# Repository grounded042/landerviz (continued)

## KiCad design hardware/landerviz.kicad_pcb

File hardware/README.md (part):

# LanderViz revision-A hardware

**2026-11-07:** the reviewed [PGA2350 carrier](carrier/README.md) Rev A
bare boards are ordered from OSH Park. The 90 × 75 mm two-layer design is
frozen; see [order status](carrier/ORDER_STATUS.md),
[manufacturing release](carrier/releases/rev-a/README.md) and
[parts sourcing](carrier/SHOPPING.md). The processor purchase assumes A4
silicon; user assembly and the PGA2350 firmware port remain ahead.
Open [the carrier project](carrier/landerviz-carrier.kicad_pro) in KiCad.
The existing `landerviz.kicad_*` files and historical sections below remain
the preserved bare-RP2354A candidate, which was not ordered.

This directory contains the KiCad 10 schematic and, after schematic approval,
the printed-circuit-board layout for LanderViz revision A.

The source of truth for requirements and open decisions is
[`../PCB.md`](../PCB.md). Do not infer electrical decisions from a footprint or
unfinished sheet when `PCB.md` still marks the item open.

## Tooling

The project currently targets KiCad 10.0.6, the version installed on the
design Mac. Firmware and software continue to use the repository's Nix flake.
The pinned Nix package set marks KiCad broken on Apple Silicon, so KiCad is not
added to the development shell until that package is usable. Open
`landerviz.kicad_pro` with the installed KiCad application.

Generated backups, lock files, and working manufacturing outputs are ignored.
The exact ordered carrier Gerber ZIP and its manifest are preserved under
`carrier/releases/rev-a/`. Source
schematics, board files, symbol/footprint libraries, design rules, and reviewed
fabrication settings belong in version control.

The project-local `sym-lib-table` and `fp-lib-table` deliberately name only the
KiCad libraries used by the capture. They also make command-line checks and a
fresh checkout independent of this Mac's global KiCad-library preferences.
`landerviz.kicad_sym` contains the reviewed TPS25821 and TLV75533PDBV pin
definitions, RP2354A, and the approved TPS22953DQC input-switch definition.
The schematic is ordinary KiCad source; opening or editing it
does not run Python or install a Python package.

## Upstream electrical reference

Raspberry Pi's `RP2350A Minimal` KiCad design R4-S1 (July 2026) is a read-only
reference for circuitry shared with RP2354A:

- <https://pip.raspberrypi.com/documents/RP-010328-CA-RP2350A%20Minimal%20KiCAD.zip>
- SHA-256:
  `c0b858d78f56fa271a827064198e8ee81e4ec246234ce6659be8a1fcd877d06b`
- License: MIT, Copyright Raspberry Pi Ltd 2026

The archive is not vendored. Its local processor regulator placement is used
as a reference-derived layout input, with attribution in `REFERENCE_LICENSE.txt`.
The complete reference board is not copied. In particular, do not copy its external QSPI flash,
Micro-USB connector, board outline, or routing. LanderViz uses RP2354A with 2
MB of in-package flash. See `PCB.md` for the exact reuse boundary.

## Capture plan

The initial hierarchy deliberately separates review domains:

| Sheet | Responsibility |
|---|---|
| `mcu.kicad_sch` | RP2354A, 12 MHz clock, core supply, decoupling, RUN, BOOTSEL, and SWD |
| `usb_power.kicad_sch` | both USB-C ports, native and PIO USB data paths, 5 V protection/switching, 3.3 V regulation, and bulk capacitance |
| `audio.kicad_sch` | stereo TRS input, per-channel bias, protection, anti-alias filters, ADC inputs, and test points |
| `controls_display.kicad_sch` | EC11 encoder, push switch, I2C level translation, and LCD connector |

Capture proceeds in reviewable slices. Component values that remain open in
`PCB.md` must be selected from calculations and manufacturer documentation,
not copied from an unrelated example.

## Current capture status — 2026-11-02

### Physical layout draft — 2026-11-04

Open `landerviz.kicad_pcb` in KiCad's PCB Editor. All 79 schematic footprints
now have working positions inside the 48 by 42 mm outline and retain their
original schematic paths, component fields, and pad connections. Three
board-only M2 mounting holes are provisional. All purchased components are
on top; the twelve bare test pads are on the underside, without adding an
assembly operation. The user approved larger and rectangular outline studies.
The regulator, crystal, processor supplies, USB, stereo audio, display,
encoder, and service connections are routed on the approved four-layer board.

Upstream USB-C and the audio jack face left. Moonlander USB-C faces right,
opposite the inputs. The display connector's opening faces outward at the top
edge, and the encoder is at the lower right. The audio jack
requires an edge notch, which is included in the draft outline. The layout
now uses four copper layers. Physical packing fits; electrical placement and routing are
still under review. The power blocks are now local, and the analog and display
groups are closer to their target positions than in the 40 mm study. Processor
bypass capacitors have priority around their respective
supply pins. Component reference text is on the fabrication layers (the assembly
drawing), keeping the tiny top side free of unreadable overlapping references.

KiCad's initial placement check reports zero schematic-parity findings (the
board components and connections match the schematic). The outline closes,
and the current placement has no courtyard overlaps, shorts, or copper-edge
clearance findings. A courtyard is the reserved assembly space around a part.
The board has zero unconnected findings. The USB locating-hole clearances
and library mismatches are resolved; see `LIBRARY_CHANGES.md` for the exact
local variants. The processor's farthest core-supply bypass, C10, is now
4.7 microfarads, as required by the datasheet, and closer to pin 23.
Ground copper fills all four layers and is joined by
stitching vias; there are no disconnected ground findings. A stitching via
is a plated hole that joins ground copper on the two sides.
There are no shorts, trace-clearance failures, courtyard overlaps, or
schematic-parity findings. No findings were waived. USB geometry/impedance, power, analog, and
assembly reviews also remain necessary.
This draft is not manufacturing-ready.

### Four-layer stack and checks — 2026-11-04

The selected working stack is JLCPCB's nominal 1.6 mm `JLC04161H-3313`, using
the manufacturer's [published copper and insulation dimensions](https://jlcpcb.com/impedance):

| Position | KiCad layer | Role |
|---|---|---|
| Top | `F.Cu` | components, local power/analog connections, USB escapes, ground fill |
| Inner 1 | `In1.Cu` | dedicated ground; no routed tracks |
| Inner 2 | `In2.Cu` | additional signal routing and ground fill |
| Bottom | `B.Cu` | existing USB/power/signal routes, bare probes, ground fill |

Outer copper is 0.035 mm; inner copper is 0.0152 mm. The insulating spacings
are 0.0994 / 1.265 / 0.0994 mm. The insulating material is FR-4, a glass/epoxy
laminate. KiCad retains nominal 1.6 mm board thickness and blue/white finish;
the 0.01 mm mask values remain rendering approximations. The selected stack
must be specified in the fabrication order, not left to an arbitrary stack.

`In1.Cu` fills as one connected ground region. The regulator has named
inner-layer keepouts beneath the inductor and switching node, following
RP2350 datasheet section 6.3.8.1 / Figure 27. The top-side fill keepout follows
the existing switching polygon's edge so that the required LX connection
remains intact. The reference regulator's component placement is retained.
C10 is corrected to the datasheet's 4.7 microfarad bypass for DVDD pin 23.

New escapes use ordinary 0.4 mm diameter / 0.2 mm drilled through vias;
these span all four layers. The project's minimum drill and via diameters now
match those values, within JLCPCB's [published capabilities](https://jlcpcb.com/capabilities/pcb-capabilities/).
The minimum annular ring remains 0.1 mm and general copper clearance 0.2 mm.
There are no blind/buried vias or newly assumed filling/capping processes.
This also resolves the previous three 0.2 mm controller-hole drill findings.

C12 moved 0.1 mm upward, with its ground via also moved upward. The right ADC
probe now connects through a small via inside the bare bottom test pad, with
shorter inner-layer branches to the series resistor and clamp. The probe has
no solder-paste aperture. Obsolete display-data detours and trial stubs were
removed. The LCD SDA via at (27.8, 8.8) mm moved to (27.8, 8.9) mm to improve
the ground reference beneath the downstream USB data pair.

Validation with KiCad 10.0.6: zero unconnected items, shorts, trace-clearance
errors, courtyard overlaps, dangling tracks/vias, or schematic-parity findings.
A separate geometric check sampled USB track centers and edges every 0.1 mm,
excluding 0.8 mm around USB via launches: all 3,798 samples have ground on
the adjacent inner layer. This verifies sampled reference coverage; it does
not establish 90-ohm differential impedance or USB electrical compliance.

### Board artwork

The working finish is blue solder mask with white silkscreen. Solder mask is
the protective coating over the copper; silkscreen is the printed lettering.
Both sides use those colors in the KiCad stackup. Enable "Use board stackup
colors" in the 3D Viewer if local appearance settings override them. The
fabrication order must separately select the desired color; the preview does
not place or configure an order. Black remains an acceptable alternative, but
mask clearances must be reviewed for that manufacturing option before release.
The stackup retains nominal 1.6 mm thickness with 35 micrometer outer and
15.2 micrometer inner copper; fabrication settings remain unreleased.

The underside has a bold `LANDERVIZ` wordmark centered at (27, 21) mm from
the upper-left board corner, with `REV A / AUDIO IN. LIGHT OUT.` at (27, 23.5)
mm. The ink clears the probe labels and through-hole hardware. The lander and flowing-ribbon
drawings were removed at the user's request. Decorative drawings are deferred
while the electrical layout is developed. Final routing and test access take
priority over ink. Press Alt+3 in the PCB Editor for KiCad's 3D Viewer and turn
the board over to inspect it; top-side service labels will be finalized after
placement stabilizes.

### Electrical placement review — continuation

The initial 40 mm physical packing was rejected because it did not adequately
preserve local power and analog circuits. See `PLACEMENT_REVIEW.md` for that
history, the subsequent outline comparison, and current routing status. A clean
overlap check must not be presented as complete electrical placement approval.
The current 48 by 42 mm draft follows the user's permission to explore larger
and rectangular outlines.

The processor regulator group now follows the local geometry of the pinned
Raspberry Pi R4-S1 reference, adjusted for this project's pad/courtyard sizes.
Its marked inductor terminal remains connected to the switch node. The crystal
signal paths are routed on top without signal vias. The local regulator
input/feedback/output, switching-node copper, filtered supply, and capacitor
ground returns are now connected. Most processor supply pins now have short
branches to their bypass capacitors, whose ground ends join the back plane.
The U1 pin 20 / C14 supply escape is now connected by a back-side branch;
the clock remains on top and the ground plane stays connected. The wider
3.3 V and 1.1 V distribution is connected. The main input fuse, protected 5 V
trunk, keyboard power switch and bulk reservoir, switched keyboard output,
and fused display feed are now connected. Short 0.25–0.4 mm pad escapes join
0.8–1.0 mm trunks; paired 0.8/0.4 mm vias carry the keyboard output between
layers. These widths need final current/temperature review before release.
The project's minimum trace width is now 0.15 mm for fine-pitch escapes; default
net-class routing width stays at 0.2 mm and local regulator power traces at
0.4 mm. Fabrication-rule signoff remains pending.

`landerviz.kicad_dru` permits 0.10 mm clearance only between the switching
node and C6/C7 pads, allowing the reference-style escape through their pad
gap. Other clearance rules remain unchanged. The local rule is based on
[JLCPCB's 1 oz pad-to-track capability](https://jlcpcb.com/capabilities/pcb-);
changing copper weight requires rechecking it. No findings are suppressed.

Four 0.3 mm drill ground vias join the processor's exposed pad (the large
ground contact underneath the chip) to the back plane. Their interaction with
solder paste and possible solder wicking through the holes must be checked
in assembly review; no premium filled/capped-via process has been selected.

The upstream USB-C A6/B6 and A7/B7 contacts are connected to their respective
data nets and to U3's electrostatic-discharge protection pads. The alternating
contacts join on opposite sides of the connector tail row, avoiding crossed
data nets. U3 has a local ground via. Both upstream and downstream data paths
now continue through their series resistors to the processor. Each signal uses
two layer transitions in the upstream link and four in the downstream link.
The processor-end vias sit outside the exposed pad, under the package body,
with tented mask rather than premium filled/capped vias. Main connector power
is routed. Configuration-channel (CC) wiring is connected on both ports.
The power controller's reference
resistor is connected. Whole-link geometry and impedance review are pending.
This is connectivity/clearance progress, not functional USB or signal-integrity
signoff; the board is not ready to power or order.

Both audio coupling capacitors now face their negative input terminals toward
the jack. C29 moved beside the right analog-to-digital converter (ADC) input.
Both filter-capacitor-to-processor paths stay on the front; the right-channel
resistor/clamp branches use the back as well. Bias, protection, filter ground
returns, and all four audio test pads are connected. Longer analog branches,
probe stubs, and their return paths remain electrical-review items.

The display clock, encoder A, debug clock/data, and reset escapes are now
connected. Display pull-up links, display data, encoder B/press, spare GPIO
probes, and boot-select are connected. R22 is now
at (38.5, 1.8) mm. Ground stitching resolved pockets created by back-side control traces;
the ground fills discard isolated copper. USB shield lugs, the display ground
pin, and U2's three thermal holes use selected solid ground connections, with
solderability still to review. No design-rule findings were waived.

Clipped package-outline ink was removed from the board; the assembly drawings
are retained, and a smaller processor pin-one dot replaces the clipped marker.
The project-owned encoder and inductor footprints retain these changes in
their source files. The edited upstream-library footprints now have matching
project-local variants. A spare-GPIO trace was rerouted around
the audio jack's non-plated mounting hole.

The user approved and the board now implements four copper layers with the
same outline and components. Earlier two-layer experiments that introduced
excessive analog detours or ground fragmentation were discarded. Those
experiments do not prove that a two-layer design is impossible.

The original same-edge USB arrangement and inward-facing LCD opening were
corrected after visual review. The local regulator block and its first traces
were moved to accommodate the left-edge USB input, USB protection was placed
behind that connector, and the probe pads were rechecked against the relocated
through-hole hardware. Pin assignments and the schematic are unchanged.

Underside probe labels: `CLK`/`DIO` are Serial Wire Debug clock/data;
`BL`/`BR` are left/right bias; `AL`/`AR` are left/right analog-to-digital
converter inputs; `GP6`/`GP7` are spare GPIO6/GPIO7 pads. The schematic test-point
references remain visible on the bottom fabrication layer.

The enclosure will be designed after the PCB is ordered, using the user's
library makerspace or a friend's 3D printer. No enclosure supplier is selected.

### MCU core

The MCU-core sheet is populated and the project-level MCU sheet symbol exposes
the frozen USB, audio, encoder, and display signals. The capture
includes the RP2354A, its 1.1 V switching-regulator network, supply bypassing,
12 MHz crystal, BOOTSEL and reset buttons, Serial Wire Debug (SWD) pads, native
USB and PIO-USB series resistors, and explicit no-connect flags on unused pins.

The exact L1 inductor, Y1 crystal, reset/BOOTSEL switches, RP2354A, and ordinary
passives now have manufacturer, JLCPCB/LCSC catalog, and footprint assignments.
L1 uses a project-local footprint copied from Abracon's land pattern; its marked
terminal is **pad 1, the +1V1 output side**, matching Raspberry Pi's R4-S1
reference. The fabrication dot was corrected after independent review; the
assembler must verify the physical dot orientation, not just the placement
rotation number. C6/C7/C9/C10 now specify the reference-design Murata
`GRM155R60J475ME47D` (JLCPCB `C82453`) instead of the unqualified CCTC
substitute. C9 has an independent ground via; the switching return uses two
adjacent vias. See [`REVIEW_RESOLUTION.md`](REVIEW_RESOLUTION.md).
The Serial Wire Debug (SWD)
and rail test points are 2 mm exposed surface pads and require no purchased
component.

### USB and power

The USB/power sheet is electrically captured and connected to the MCU sheet:

- J1 is the upstream USB-C sink/device port. Each configuration-channel (CC)
  pin has its own 5.1 kilohm pull-down; the two orientation copies of each USB
  data signal join before the MCU's 27 ohm series resistor.
- J2 is the downstream USB-C source/host port. A TPS25821 monitors both CC
  pins, advertises 1.5 A, and switches the keyboard's 5 V VBUS rail only after
  attachment. Both connector orientations join before the MCU's 22 ohm series
  resistors.
- Each USB data pair has a TPD2EUSB30DRTR two-channel electrostatic-discharge
  (ESD) protector. ESD means a short high-voltage event such as a static shock.
- A stocked 2 A-hold LUTE `1206L200/16NR` resettable polymer fuse protects the
  input. Its hold current falls to 1.42 A at 60°C, so it does not establish
  a 1.5 A continuous port rating across temperature. Supported ambient/current
  limits still require a release decision.
- The proven 470 microfarad reservoir is on the protected input side
  of the TPS25821, after the approved TPS22953 controlled-charging input
  switch. Its keyboard-port output has 4.7 microfarads, below the
  controller's 10 microfarad limit.
  C25 now sits beside J2 at (37.1,14.2) mm. U6 ramps the reservoir and every
  existing powered branch; only 1 µF bypass and the enable circuit precede it.
  Its estimated startup behavior still requires assembled-board validation.
  See [`INPUT_POWER_PROPOSAL.md`](INPUT_POWER_PROPOSAL.md) for the approved
  five-part circuit, enable threshold, ramp calculation and reverse-blocking limits.
- A TLV75533PDBVR fixed-output, 500 mA low-dropout regulator creates the 3.3 V
  logic rail. The display receives a separately protected 5 V branch.
- Labeled 5 V, 3.3 V, and ground test points are included.

The USB/power page has no electrical-rules-check findings. The exported netlist
was also checked to confirm that connector-facing data nets stop at the correct
side of each series resistor; the corresponding chip-facing nets reach only
the intended native-USB or PIO-USB pin.

Both USB-C ports use the GCT `USB4105-GF-A-060`. The TPS25821 uses a
project-local footprint built from TI's `DSS0012B` recommended WSON land pattern;
**WSON** means a very small leadless package with an exposed thermal pad. The
470 microfarad reservoir, display-branch fuse, reset/BOOTSEL switches, crystal,
inductor, and test-pad style are also assigned. Placement, cable clearance, and
assembly-orientation review remain fabrication gates, but no schematic part is
waiting for a footprint.

### Stereo audio frontend

The audio sheet is populated, electrically connected to GPIO26/ADC0 and
GPIO27/ADC1, and clean under the project-level electrical rules check. Tip is
left, ring is right, and sleeve is ground on J3. Each channel is independent:

- A 10 microfarad coupling capacitor blocks direct current from the mixer. If
  the selected part is polarized, its positive terminal faces the bias node.
- Two 22 kilohm, 1% resistors bias that node near half of 3.3 V. They present
  an approximately 11 kilohm load; with 10 microfarads, the nominal high-pass
  corner is about 1.45 Hz.
- A 10 kilohm, 1% series resistor and 2.2 nanofarad C0G, 5% capacitor form a
  first-order low-pass at about 7.2 kHz. This is intentional modest
  anti-aliasing for the firmware's 15.625 kHz-per-channel sampling, whose
  Nyquist frequency is about 7.8 kHz.
- A BAT54S-7-F dual Schottky diode in SOT-23 clamps the ADC node toward ground
  and 3.3 V. The series resistor limits fault and unpowered-input current. The
  package and ordering code match the
  [Diodes Incorporated datasheet](https://www.diodes.com/datasheet/download/BAT54S.pdf);
  leakage and assembly stock remain bill-of-materials release checks.
- TP7/TP9 expose the left/right bias nodes; TP8/TP10 expose the left/right ADC
  nodes.

J3 is frozen as the CUI `SJ1-3523N` right-angle through-hole jack using KiCad's
matching `Jack_3.5mm_CUI_SJ1-3523N_Horizontal` footprint. JLCPCB/LCSC catalog
identifier `C20182914` records the sourcing target; assembly inventory must be
rechecked when the order is released. C26/C27 are polarized 10 microfarad,
16 V surface-mount electrolytics, with the positive terminal toward the biased
ADC node. Audio test points use the same 2 mm exposed pads as the power and SWD
points. Assembled-board bring-up must confirm bias voltage, silence/noise,
bass response, high-frequency texture, and clipping before firmware gain or
calibration constants are retuned.

### Encoder and external display

The controls/display sheet now captures the proven encoder circuit and
revision-A serial-display interface:

- SW3 is frozen as the top-facing Bourns `PEC12R-4120F-S0012`, JLCPCB/LCSC
  `C143801`: 12 detents, 12 pulses, a push switch, and a 20 mm shaft. It
  connects encoder A, encoder B, and the push switch to GPIO4, GPIO5, and
  GPIO8. Its encoder common and other switch terminal return to digital ground.
  Firmware supplies all three pull-ups and debounce/decoding; the PCB adds no
  filtering that could change the validated behavior. This no-bushing variant
  requires PCB/enclosure support close to the control so that repeated pushes
  do not flex the board.
- Q1 and Q2 are BSS138 N-channel MOSFETs
  (metal-oxide-semiconductor field-effect transistors) in SOT-23
  (small-outline transistor) packages. Their sources face the 3.3 V MCU bus,
  drains face the 5 V display bus, and gates connect to 3.3 V. This is the same
  bidirectional open-drain I2C (Inter-Integrated Circuit) level-shifter
  topology demonstrated by the breadboard breakout. The schematic pin order
  matches the
  [onsemi BSS138 datasheet](https://www.onsemi.com/download/data-sheet/pdf/bss138-d.pdf).
- R20/R21 are populated 4.7 kilohm, 1% pull-ups on the 3.3 V side. R22/R23 are
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
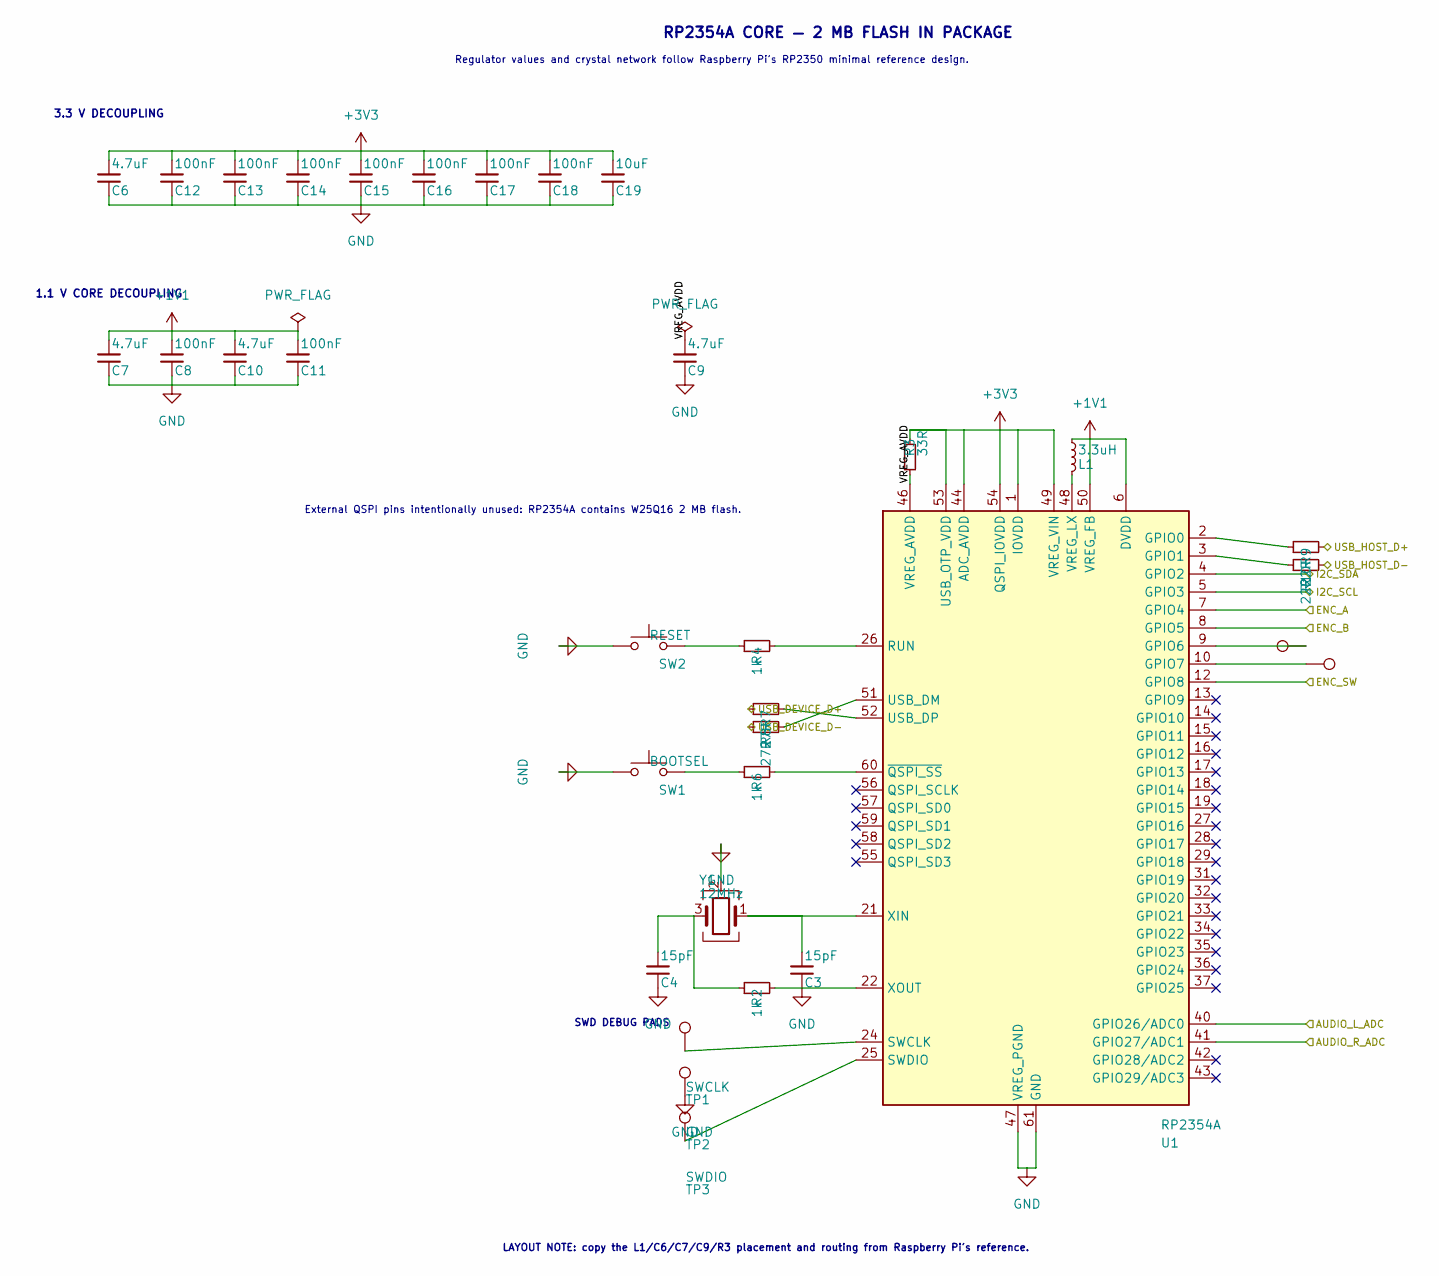
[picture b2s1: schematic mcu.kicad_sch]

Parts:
C3, C4: 15pF; C_0402_1005Metric; MPN 0402CG150J500NT; LCSC C1548
C6, C7, C9, C10: 4.7uF; C_0402_1005Metric; MPN GRM155R60J475ME47D; LCSC C82453
C8, C11, C12, C13, C14, C15, C16, C17, C18: 100nF; C_0402_1005Metric; MPN CL05B104KO5NNNC; LCSC C1525
C19: 10uF; C_0402_1005Metric; MPN TCC0402X5R106M6R3ATR; LCSC C48543727
L1: 3.3uH; L_Abracon_AOTA-B201610S3R3-101-T; MPN AOTA-B201610S3R3-101-T; LCSC C42411119
R2, R4, R6: 1k; R_0402_1005Metric; MPN 0402WGF1001TCE; LCSC C11702
R3: 33R; R_0402_1005Metric; MPN 0402WGF330JTCE; LCSC C25105
R7, R8: 27R; R_0402_1005Metric; MPN 0402WGF270JTCE; LCSC C25100
R9, R10: 22R; R_0402_1005Metric; MPN 0402WGF220JTCE; LCSC C25092
SW1: BOOTSEL; SW_Push_1P1T_XKB_TS-1187A; MPN TS-1187A-B-A-B; LCSC C318884
SW2: RESET; SW_Push_1P1T_XKB_TS-1187A; MPN TS-1187A-B-A-B; LCSC C318884
TP1: SWCLK; TestPoint_Pad_D2.0mm
TP2: GND; TestPoint_Pad_D2.0mm
TP3: SWDIO; TestPoint_Pad_D2.0mm
TP11: GPIO6; TestPoint_Pad_D2.0mm
TP12: GPIO7; TestPoint_Pad_D2.0mm
U1: RP2354A; QFN-60-1EP_7x7mm_P0.4mm_EP3.4x3.4mm_LanderViz; MPN RP2354A; LCSC C41378174
Y1: 12MHz; Crystal_SMD_3225-4Pin_3.2x2.5mm; MPN ABM8-272-T3; LCSC C20625731

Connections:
+1V1: C7.1, C8.1, C10.1, C11.1, L1.1, U1.6 (DVDD), U1.23 (DVDD), U1.39 (DVDD), U1.50 (VREG_FB)
+3V3: C6.1, C12.1, C13.1, C14.1, C15.1, C16.1, C17.1, C18.1, C19.1, R3.1, U1.1 (IOVDD), U1.11 (IOVDD), U1.20 (IOVDD), U1.30 (IOVDD), U1.38 (IOVDD), U1.44 (ADC_AVDD), U1.45 (IOVDD), U1.49 (VREG_VIN), U1.53 (USB_OTP_VDD), U1.54 (QSPI_IOVDD); also elsewhere on the board
/Audio frontend/AUDIO_L_ADC: U1.40 (GPIO26/ADC0); also elsewhere on the board
/Audio frontend/AUDIO_R_ADC: U1.41 (GPIO27/ADC1); also elsewhere on the board
/ENC_A: U1.7 (GPIO4); also elsewhere on the board
/ENC_B: U1.8 (GPIO5); also elsewhere on the board
/ENC_SW: U1.12 (GPIO8); also elsewhere on the board
/I2C_SCL: U1.5 (GPIO3); also elsewhere on the board
/I2C_SDA: U1.4 (GPIO2); also elsewhere on the board
/MCU core/VREG_AVDD: C9.1, R3.2, U1.46 (VREG_AVDD)
/USB and power/USB_DEVICE_D+: R7.1; also elsewhere on the board
/USB and power/USB_DEVICE_D-: R8.1; also elsewhere on the board
/USB and power/USB_HOST_D+: R9.2; also elsewhere on the board
/USB and power/USB_HOST_D-: R10.2; also elsewhere on the board
unnamed: C4.1, R2.1, Y1.3
unnamed: R4.1, SW2.2
unnamed: R6.1, SW1.2
unnamed: R9.1, U1.2 (GPIO0)
unnamed: R10.1, U1.3 (GPIO1)
unnamed: TP11.1, U1.9 (GPIO6)
unnamed: TP12.1, U1.10 (GPIO7)
unnamed: R4.2, U1.26 (RUN)
unnamed: TP1.1, U1.24 (SWCLK)
unnamed: TP3.1, U1.25 (SWDIO)
unnamed: R8.2, U1.51 (USB_DM)
unnamed: R7.2, U1.52 (USB_DP)
unnamed: L1.2, U1.48 (VREG_LX)
unnamed: C3.1, U1.21 (XIN), Y1.1
unnamed: R6.2, U1.60 (~QSPI_SS)

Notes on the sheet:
RP2354A CORE — 2 MB FLASH IN PACKAGE
Regulator values and crystal network follow Raspberry Pi's RP2350 minimal reference design.
3.3 V DECOUPLING
1.1 V CORE DECOUPLING
SWD DEBUG PADS
External QSPI pins intentionally unused: RP2354A contains W25Q16 2 MB flash.
LAYOUT NOTE: copy the L1/C6/C7/C9/R3 placement and routing from Raspberry Pi's reference.

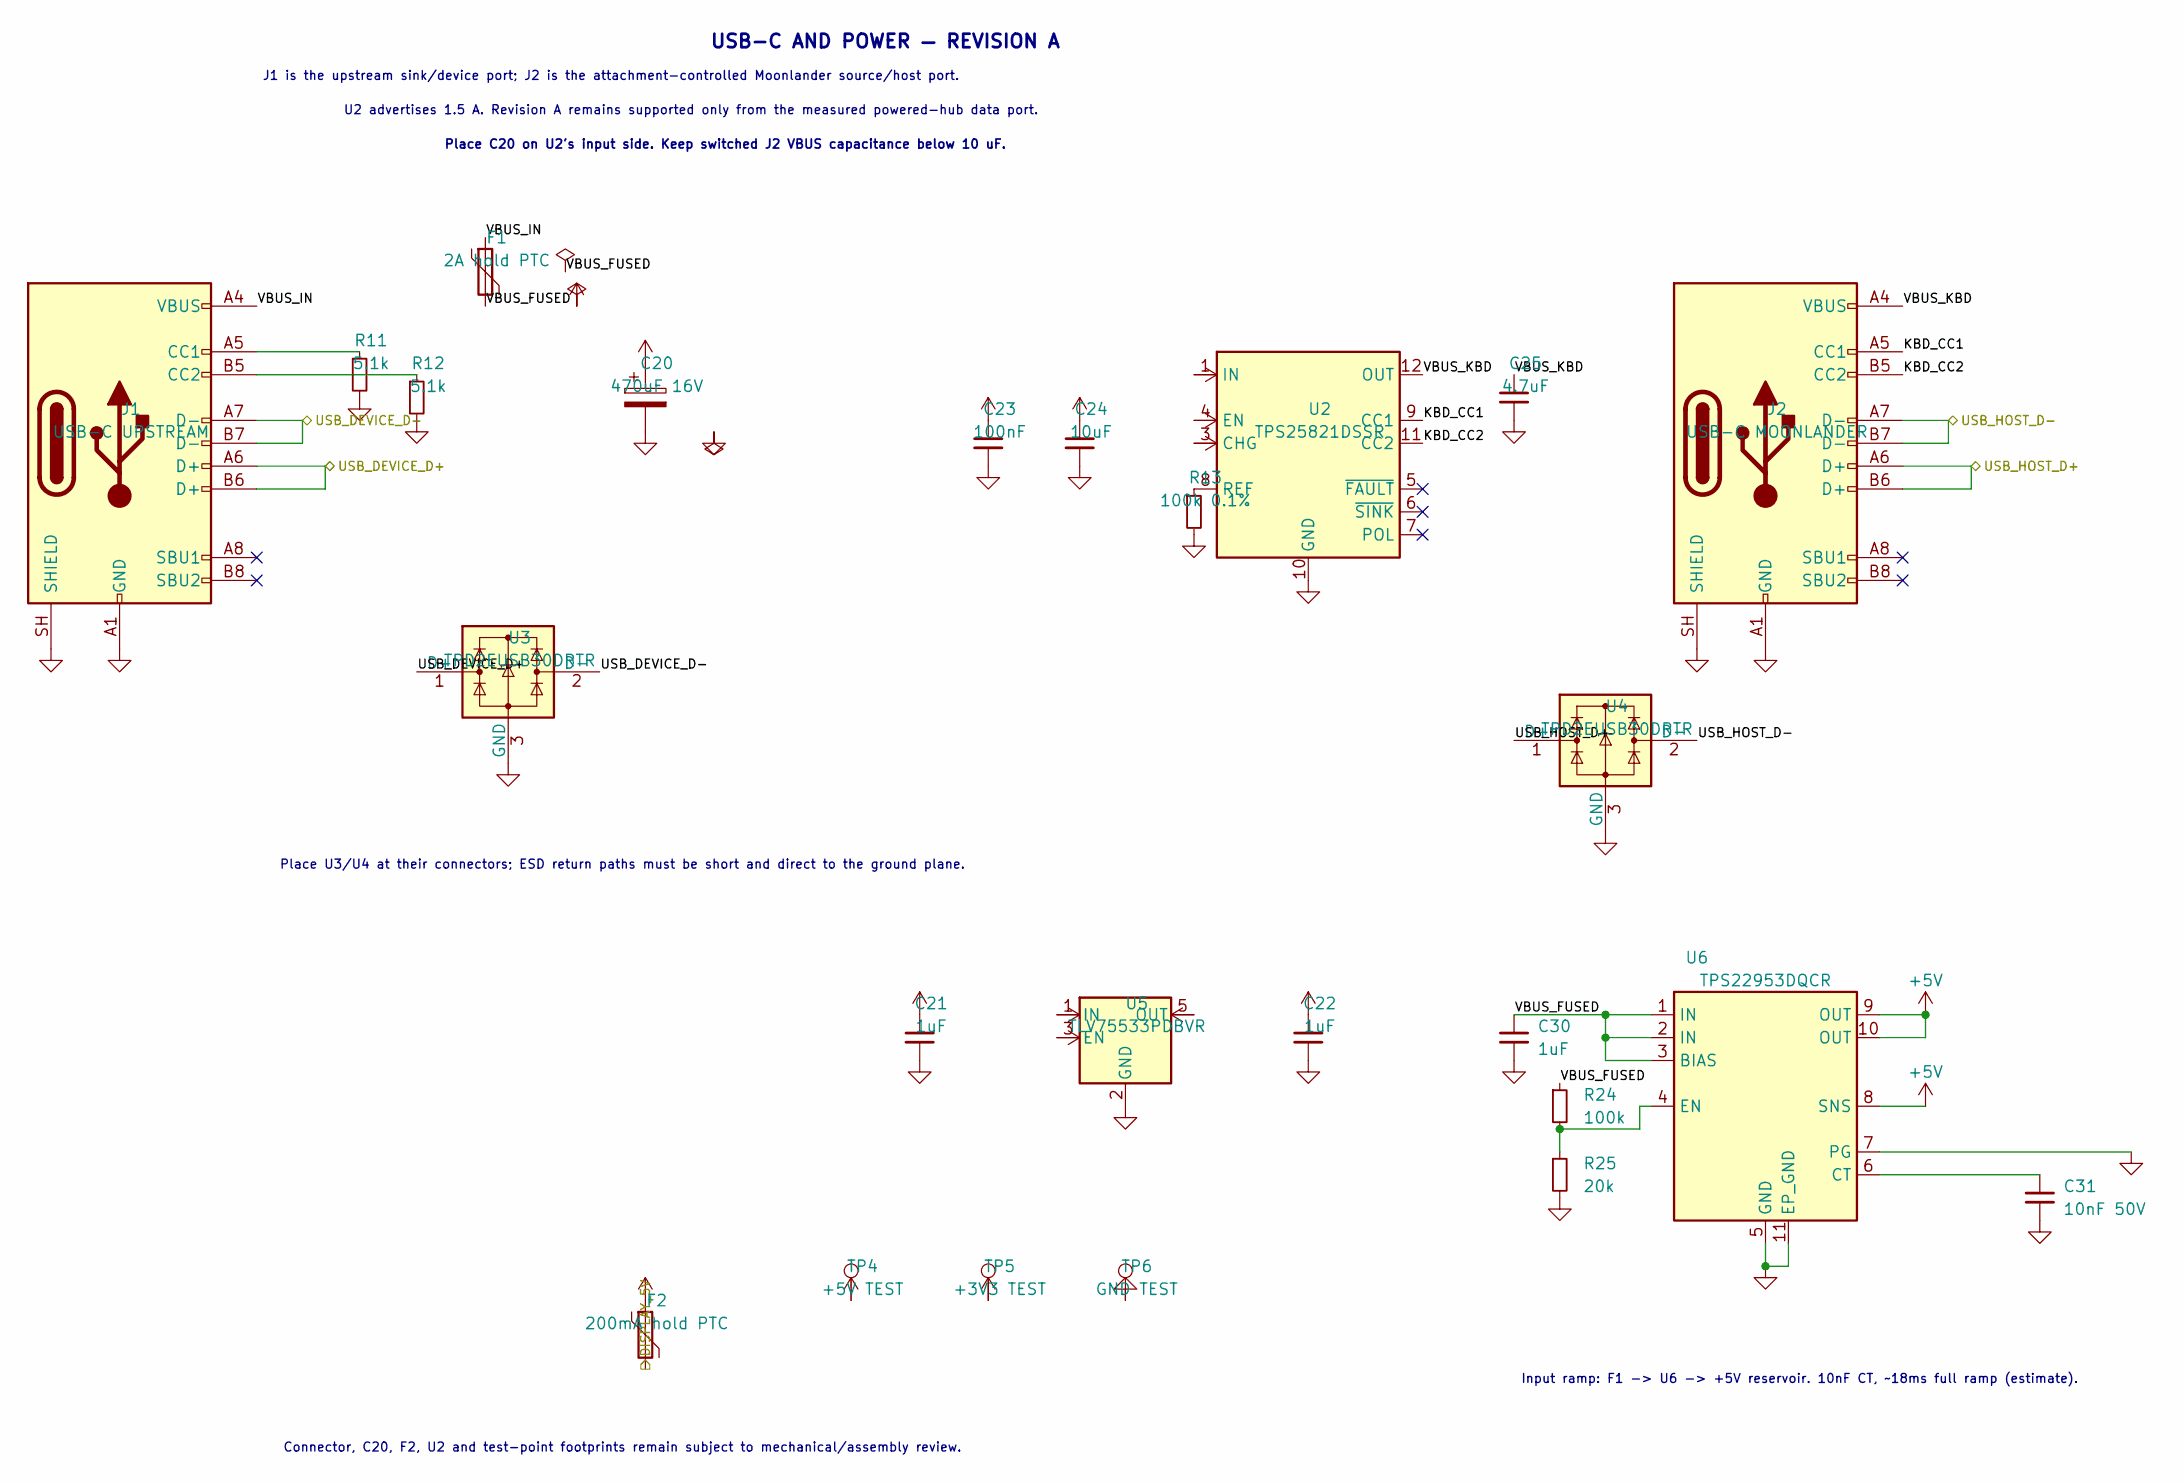
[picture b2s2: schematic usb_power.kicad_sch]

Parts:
C20: 470uF 16V; CP_Elec_8x10.5; MPN RVT1C471M0810; LCSC C3341
C21, C22, C30: 1uF; C_0603_1608Metric; MPN CL10A105KA8NNNC; LCSC C5673
C23: 100nF; C_0402_1005Metric; MPN CL05B104KO5NNNC; LCSC C1525
C24: 10uF; C_0805_2012Metric; MPN TCC0805X7R106K160FT; LCSC C380347
C25: 4.7uF; C_0603_1608Metric; MPN CL10Y475KP96PNC; LCSC C22371067
C31: 10nF 50V; C_0402_1005Metric; MPN CL05B103KB5NNNC; LCSC C15195
F1: 2A hold PTC; Fuse_1206_3216Metric; MPN 1206L200/16NR; LCSC C22374899
F2: 200mA hold PTC; Fuse_0603_1608Metric; MPN 0603L020YR; LCSC C207011
J1: USB-C UPSTREAM; USB_C_GCT_USB4105_LanderViz; MPN USB4105-GF-A-060; LCSC C3025063
J2: USB-C MOONLANDER; USB_C_GCT_USB4105_LanderViz; MPN USB4105-GF-A-060; LCSC C3025063
R11, R12: 5.1k; R_0402_1005Metric; MPN 0402WGF5101TCE; LCSC C25905
R13: 100k 0.1%; R_0402_1005Metric; MPN RT0402BRE07100KL; LCSC C136979
R24: 100k; R_0402_1005Metric; MPN 0402WGF1003TCE; LCSC C25741
R25: 20k; R_0402_1005Metric; MPN 0402WGF2002TCE; LCSC C25765
TP4: +5V TEST; TestPoint_Pad_D2.0mm
TP5: +3V3 TEST; TestPoint_Pad_D2.0mm
TP6: GND TEST; TestPoint_Pad_D2.0mm
U2: TPS25821DSSR; Texas_WSON-12-1EP_2x3mm_P0.5mm_DSS0012B; MPN TPS25821DSSR; LCSC C2861545
U3, U4: TPD2EUSB30DRTR; Texas_DRT-3; MPN TPD2EUSB30DRTR; LCSC C97502
U5: TLV75533PDBVR; SOT-23-5; MPN TLV75533PDBVR; LCSC C404027
U6: TPS22953DQCR; WSON-10-1EP_2x3mm_P0.5mm_EP0.84x2.4mm; MPN TPS22953DQCR; LCSC C471046

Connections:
+3V3: C22.1, TP5.1, U5.5 (OUT); also elsewhere on the board
+5V: C20.1, C21.1, C23.1, C24.1, F2.1, TP4.1, U2.1 (IN), U2.2 (IN), U2.3 (CHG), U2.4 (EN), U5.1 (IN), U5.3 (EN), U6.8 (SNS), U6.9 (OUT), U6.10 (OUT)
/DISPLAY_5V: F2.2; also elsewhere on the board
/USB and power/KBD_CC1: J2.A5 (CC1), U2.9 (CC1)
/USB and power/KBD_CC2: J2.B5 (CC2), U2.11 (CC2)
/USB and power/USB_DEVICE_D+: J1.A6 (D+), J1.B6 (D+), U3.1 (D+); also elsewhere on the board
/USB and power/USB_DEVICE_D-: J1.A7 (D-), J1.B7 (D-), U3.2 (D-); also elsewhere on the board
/USB and power/USB_HOST_D+: J2.A6 (D+), J2.B6 (D+), U4.1 (D+); also elsewhere on the board
/USB and power/USB_HOST_D-: J2.A7 (D-), J2.B7 (D-), U4.2 (D-); also elsewhere on the board
/USB and power/VBUS_FUSED: C30.1, F1.2, R24.1, U6.1 (IN), U6.2 (IN), U6.3 (BIAS)
/USB and power/VBUS_IN: F1.1, J1.A4 (VBUS), J1.A9 (VBUS), J1.B4 (VBUS), J1.B9 (VBUS)
/USB and power/VBUS_KBD: C25.1, J2.A4 (VBUS), J2.A9 (VBUS), J2.B4 (VBUS), J2.B9 (VBUS), U2.12 (OUT)
unnamed: J1.A5 (CC1), R11.1
unnamed: J1.B5 (CC2), R12.1
unnamed: R13.1, U2.8 (REF)
unnamed: C31.1, U6.6 (CT)
unnamed: R24.2, R25.1, U6.4 (EN)

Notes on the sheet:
USB-C AND POWER — REVISION A
J1 is the upstream sink/device port; J2 is the attachment-controlled Moonlander source/host port.
U2 advertises 1.5 A. Revision A remains supported only from the measured powered-hub data port.
Place C20 on U2's input side. Keep switched J2 VBUS capacitance below 10 uF.
Place U3/U4 at their connectors; ESD return paths must be short and direct to the ground plane.
Connector, C20, F2, U2 and test-point footprints remain subject to mechanical/assembly review.
Input ramp: F1 -> U6 -> +5V reservoir. 10nF CT, ~18ms full ramp (estimate).

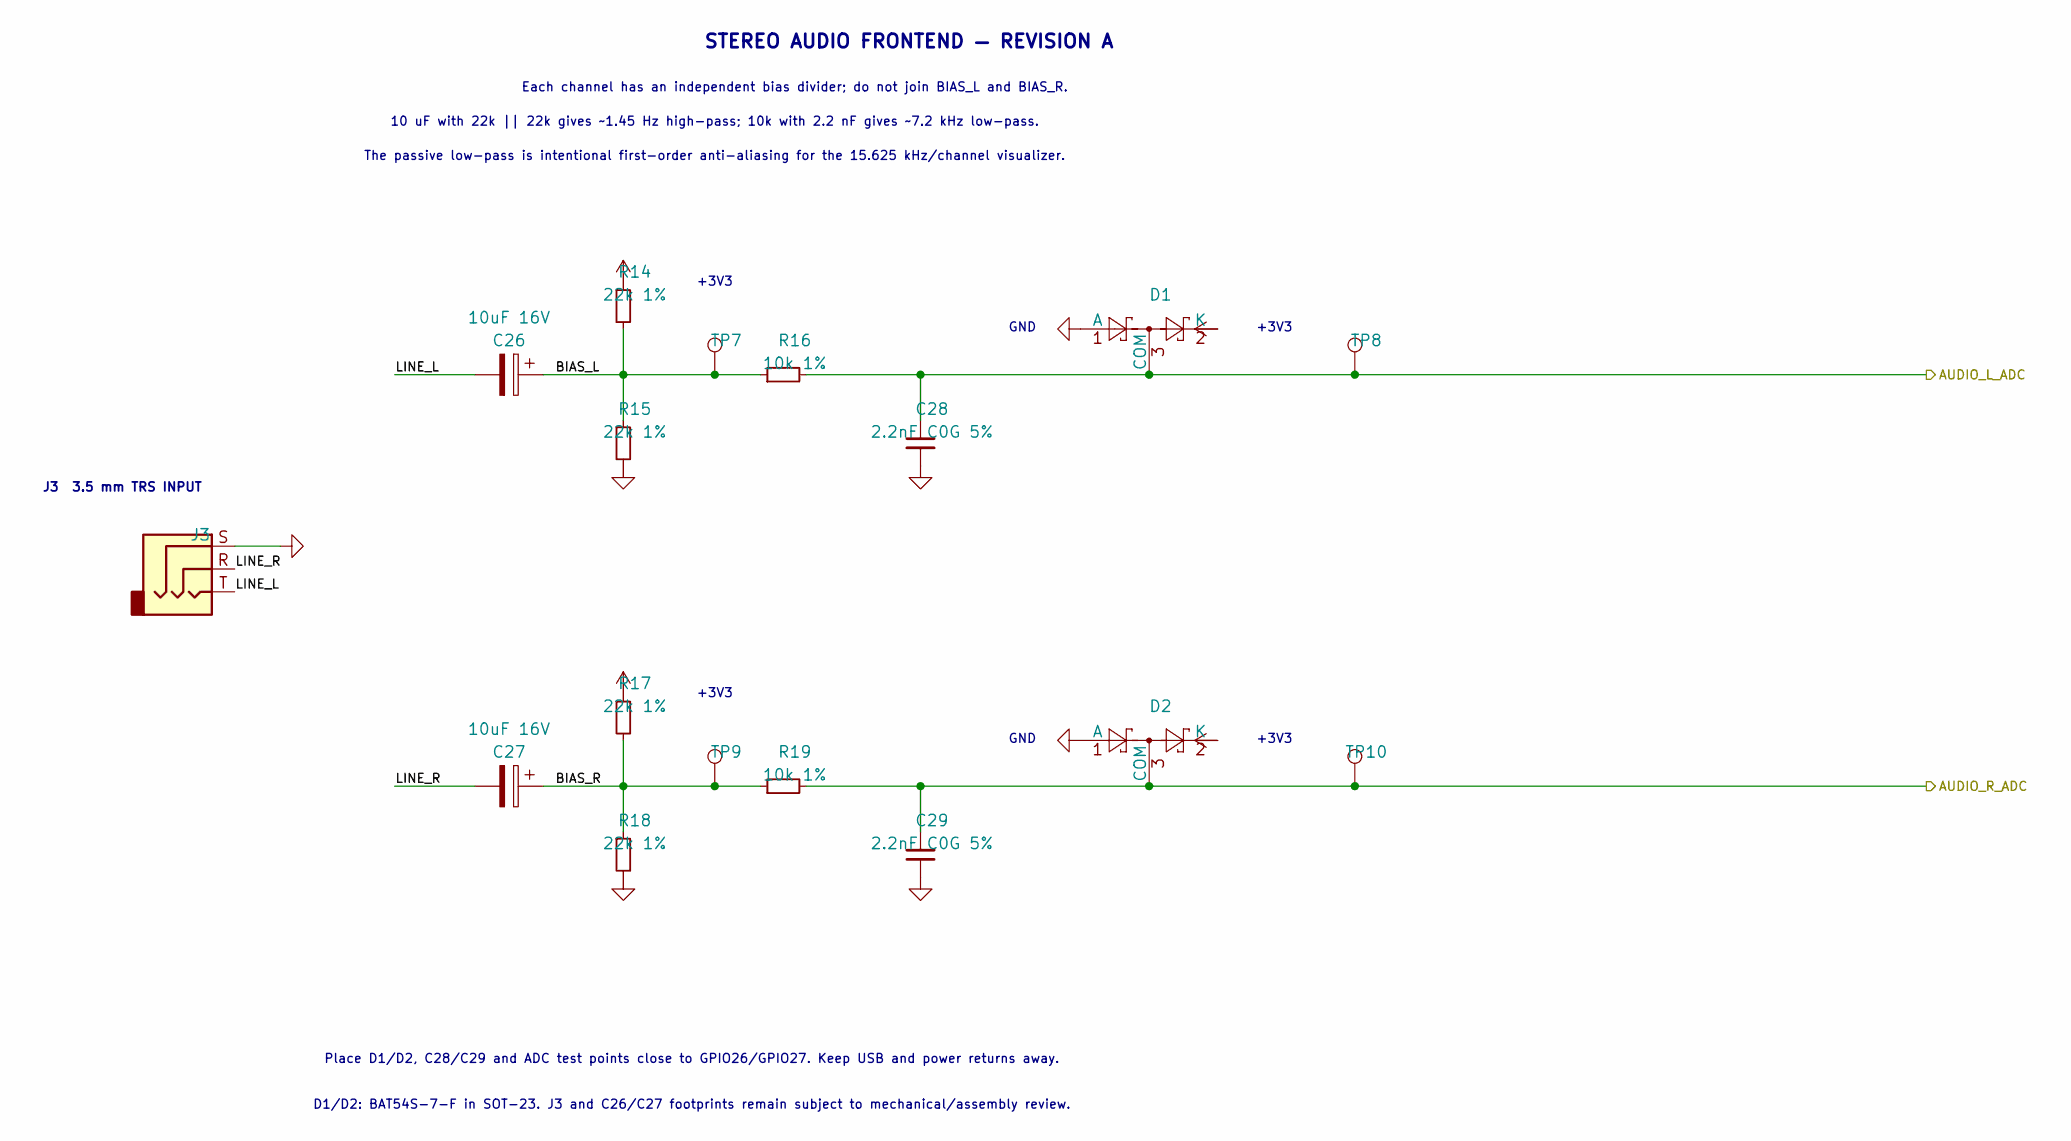
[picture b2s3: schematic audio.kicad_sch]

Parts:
C26, C27: 10uF 16V; CP_Elec_4x5.4; MPN RVT1C100M0405; LCSC C3357
C28, C29: 2.2nF C0G 5%; C_0402_1005Metric; MPN GRM1555C1H222JA01D; LCSC C385029
D1, D2: BAT54S-7-F; SOT-23; MPN BAT54S-7-F; LCSC C83574
J3: SJ1-3523N TRS INPUT; Jack_3.5mm_CUI_SJ1-3523N_Horizontal_LanderViz; MPN SJ1-3523N; LCSC C20182914
R14, R15, R17, R18: 22k 1%; R_0402_1005Metric; MPN 0402WGF2202TCE; LCSC C25768
R16, R19: 10k 1%; R_0402_1005Metric; MPN 0402WGF1002TCE; LCSC C25744
TP7: BIAS L TEST; TestPoint_Pad_D2.0mm
TP8: ADC L TEST; TestPoint_Pad_D2.0mm
TP9: BIAS R TEST; TestPoint_Pad_D2.0mm
TP10: ADC R TEST; TestPoint_Pad_D2.0mm

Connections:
+3V3: D1.2 (K), D2.2 (K), R14.1, R17.1; also elsewhere on the board
/Audio frontend/AUDIO_L_ADC: C28.1, D1.3 (COM), R16.2, TP8.1; also elsewhere on the board
/Audio frontend/AUDIO_R_ADC: C29.1, D2.3 (COM), R19.2, TP10.1; also elsewhere on the board
/Audio frontend/BIAS_L: C26.1, R14.2, R15.1, R16.1, TP7.1
/Audio frontend/BIAS_R: C27.1, R17.2, R18.1, R19.1, TP9.1
/Audio frontend/LINE_L: C26.2, J3.T
/Audio frontend/LINE_R: C27.2, J3.R

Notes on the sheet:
J3 3.5 mm TRS INPUT
+3V3
GND
STEREO AUDIO FRONTEND — REVISION A
Each channel has an independent bias divider; do not join BIAS_L and BIAS_R.
10 uF with 22k || 22k gives ~1.45 Hz high-pass; 10k with 2.2 nF gives ~7.2 kHz low-pass.
The passive low-pass is intentional first-order anti-aliasing for the 15.625 kHz/channel visualizer.
Place D1/D2, C28/C29 and ADC test points close to GPIO26/GPIO27. Keep USB and power returns away.
D1/D2: BAT54S-7-F in SOT-23. J3 and C26/C27 footprints remain subject to mechanical/assembly review.

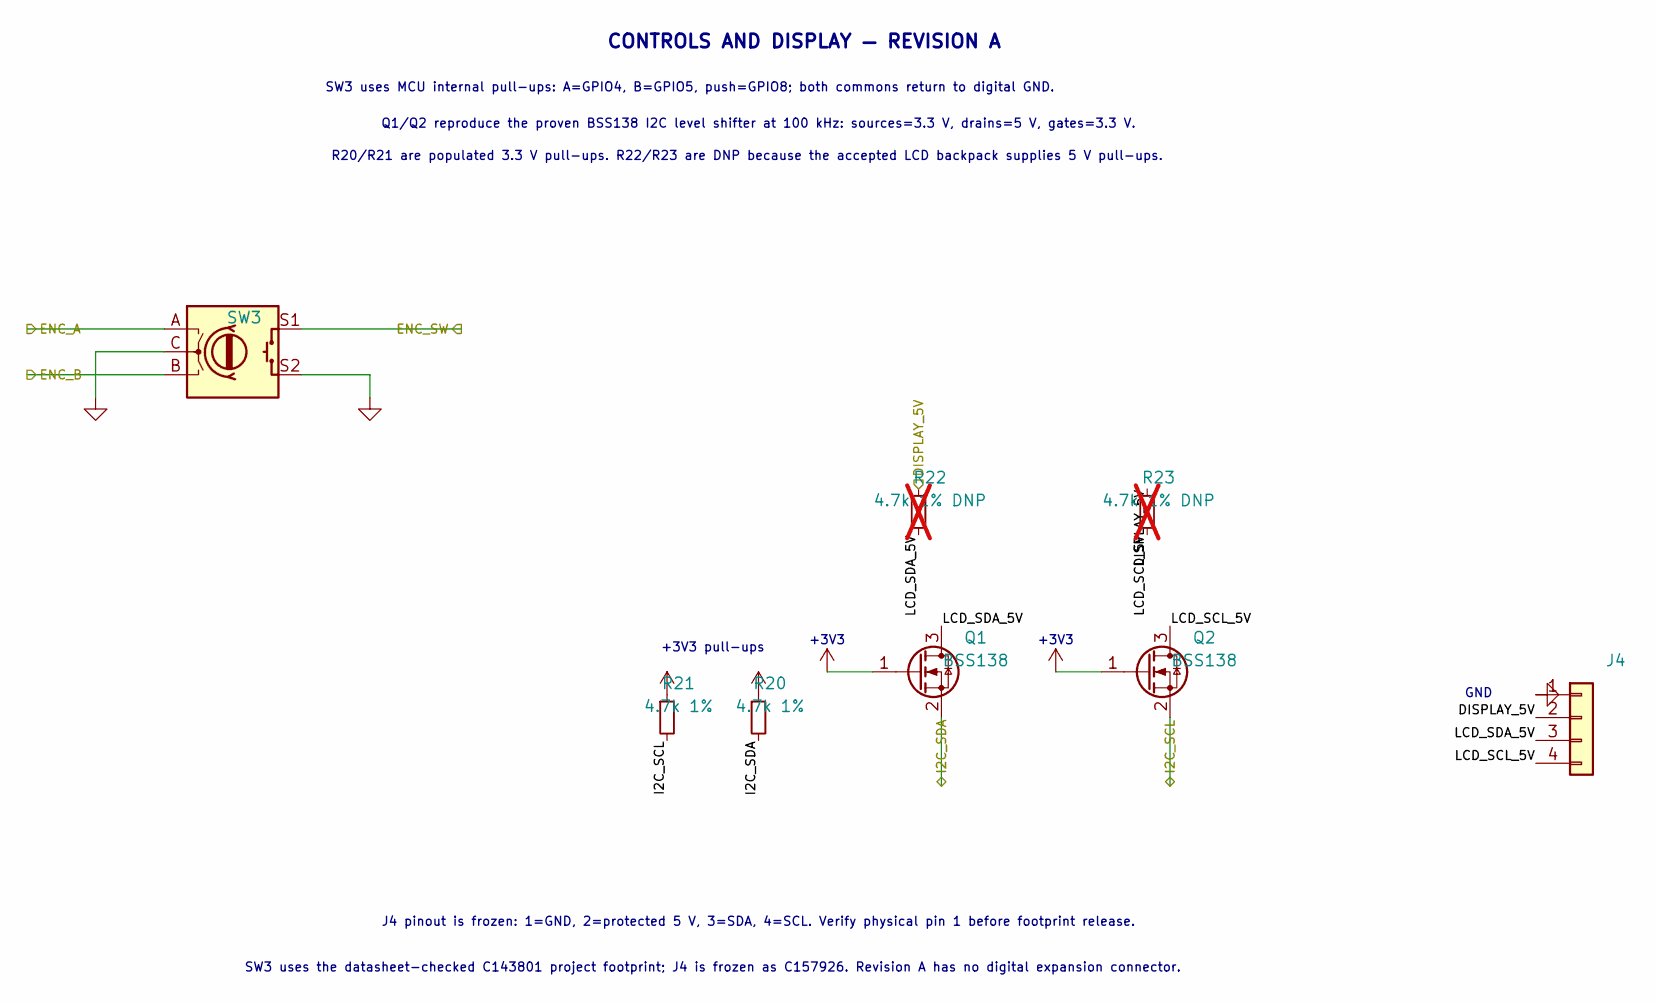
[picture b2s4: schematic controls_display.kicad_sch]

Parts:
J4: S4B-PH-K-S DISPLAY; JST_PH_S4B-PH-K_1x04_P2.00mm_Horizontal; MPN S4B-PH-K-S(LF)(SN); LCSC C157926
Q1, Q2: BSS138; SOT-23; MPN BSS138LT1G; LCSC C82045
R20, R21: 4.7k 1%; R_0402_1005Metric; MPN 0402WGF4701TCE; LCSC C25900
R22, R23: 4.7k 1% DNP; R_0402_1005Metric; MPN 0402WGF4701TCE; LCSC C25900; not fitted
SW3: PEC12R-4120F-S0012 12-detent encoder + push; RotaryEncoder_Bourns_Vertical_PEC12R-4x20F-Sxxxx; MPN PEC12R-4120F-S0012; LCSC C143801

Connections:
+3V3: Q1.1 (G), Q2.1 (G), R20.1, R21.1; also elsewhere on the board
/Controls and display/LCD_SCL_5V: J4.4, Q2.3 (D), R23.2
/Controls and display/LCD_SDA_5V: J4.3, Q1.3 (D), R22.2
/DISPLAY_5V: J4.2, R22.1, R23.1; also elsewhere on the board
/ENC_A: SW3.A; also elsewhere on the board
/ENC_B: SW3.B; also elsewhere on the board
/ENC_SW: SW3.S1; also elsewhere on the board
/I2C_SCL: Q2.2 (S), R21.2; also elsewhere on the board
/I2C_SDA: Q1.2 (S), R20.2; also elsewhere on the board

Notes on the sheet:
+3V3
+3V3 pull-ups
GND
CONTROLS AND DISPLAY — REVISION A
SW3 uses MCU internal pull-ups: A=GPIO4, B=GPIO5, push=GPIO8; both commons return to digital GND.
Q1/Q2 reproduce the proven BSS138 I2C level shifter at 100 kHz: sources=3.3 V, drains=5 V, gates=3.3 V.
R20/R21 are populated 3.3 V pull-ups. R22/R23 are DNP because the accepted LCD backpack supplies 5 V pull-ups.
J4 pinout is frozen: 1=GND, 2=protected 5 V, 3=SDA, 4=SCL. Verify physical pin 1 before footprint release.
SW3 uses the datasheet-checked C143801 project footprint; J4 is frozen as C157926. Revision A has no digital expansion connector.

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
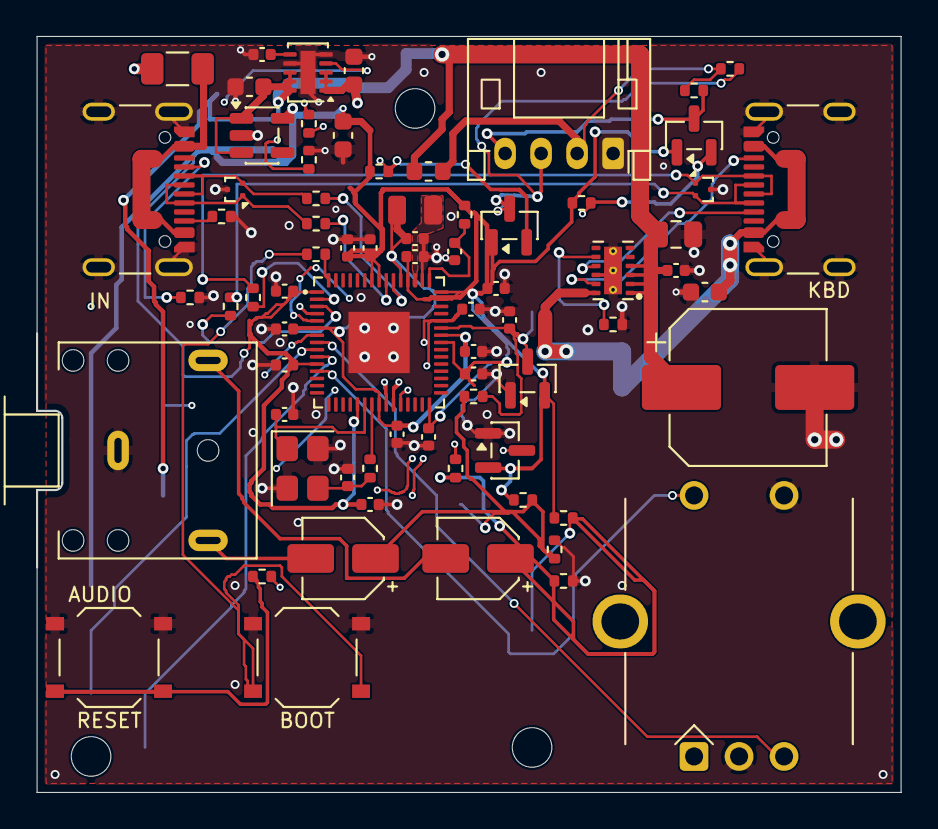
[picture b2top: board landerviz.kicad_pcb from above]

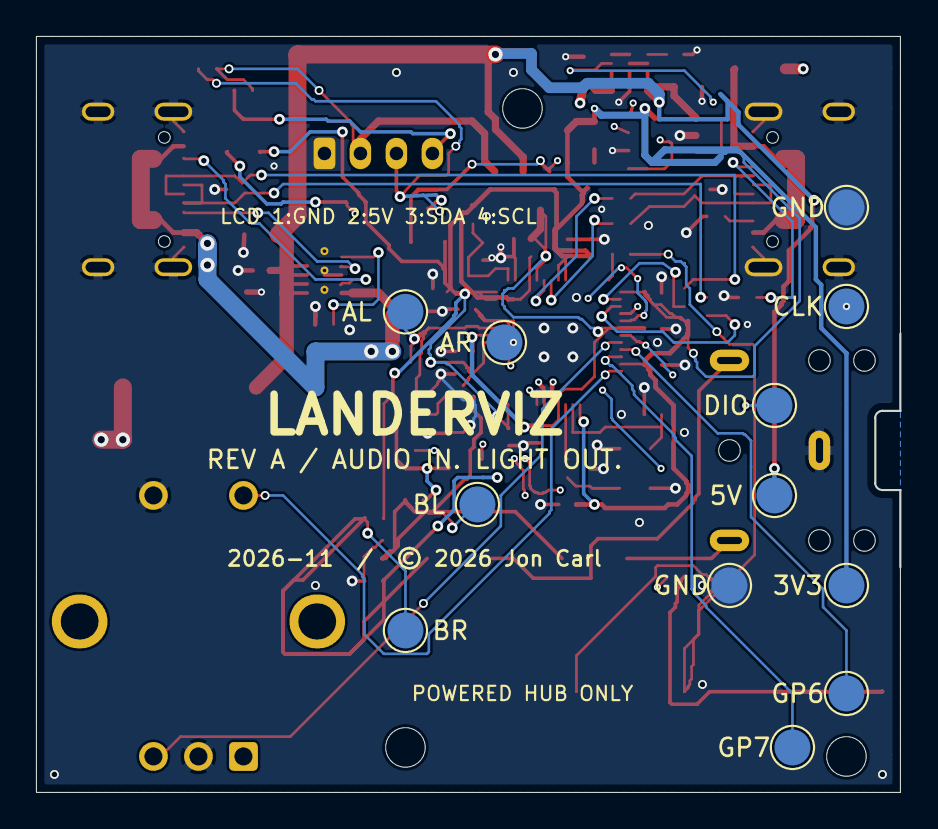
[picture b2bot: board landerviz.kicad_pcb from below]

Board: 4 copper layers, 48.0 x 42.0 mm, 87 parts (12 on the bottom side), 49 nets.

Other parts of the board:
H1, H2, H3: MountingHole_2.2mm_M2

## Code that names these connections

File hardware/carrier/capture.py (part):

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        ref='R'+str(number)
        c.instance('Device:R_Small',ref,value,x,y)
        c.connect(ref,'1',net,0,-5.08); c.connect(ref,'2',rail,0,5.08)
    for ref,pin_net,port_net,y in [('R5','HOST_GP0_DP','KBD_DP',175.26),('R6','HOST_GP1_DM','KBD_DM',190.5)]:
        c.instance('Device:R_Small',ref,'22R',50.8,y,270)
        c.connect(ref,'1',pin_net,5.08);c.connect(ref,'2',port_net,-5.08)
    c.instance('Device:C_Polarized','C1','470uF / >=10V',104.14,175.26)
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    c.instance('Connector_Audio:AudioJack3','J3','SJ1-3533NG',195.58,30.48,
               properties={'Manufacturer':'Same Sky','MPN':'SJ1-3533NG',
                           'Datasheet':'https://www.sameskydevices.com/product/resource/sj1-353xng.pdf'},ref_y=15.24)
    for pin,net in {'S':'GND','R':'LINE_R','T':'LINE_L'}.items():c.connect('J3',pin,net)
    for channel,y,refs in [('L',71.12,('C2','C3','R7','R8','R9','D1','D2')),
                           ('R',144.78,('C4','C5','R10','R11','R12','D3','D4'))]:
        cap, shunt, upper, lower, series, high, low = refs
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    converter=['LV','GND_L','LV1','LV2','LV3','LV4','HV','GND_H','HV1','HV2','HV3','HV4']
    c.module('Carrier:Level_Converter',passive(converter[:6]),passive(converter[6:]),15.24)
    c.instance('Carrier:Level_Converter','U2','Existing BSS138 module',238.76,223.52,ref_y=207.01)
    mapping={'LV':'+3V3','GND_L':'GND','LV1':'SDA_3V3','LV2':'SCL_3V3',
             'HV':'+5V','GND_H':'GND','HV1':'SDA_5V','HV2':'SCL_5V'}
    for pin in converter:c.connect('U2',pin,mapping.get(pin),-5.08 if pin in converter[:6] else 5.08)
    c.module('Carrier:LCD_Header',[],passive(['1','2','3','4']),10.16)
    c.instance('Carrier:LCD_Header','J4','LCD: GND 5V SDA SCL',297.18,223.52,ref_y=208.28)
    for pin,net in {'1':'GND','2':'+5V','3':'SDA_5V','4':'SCL_5V'}.items():c.connect('J4',pin,net)
    c.module('Carrier:Encoder',[],passive(['A','C','B','S1','S2']),10.16)
    c.instance('Carrier:Encoder','SW3','ACZ11BR1E-20FD1-12C',365.76,223.52,ref_y=207.01,
               properties={'Manufacturer':'Same Sky','MPN':'ACZ11BR1E-20FD1-12C',
                       'Datasheet':'https://www.sameskydevices.com/product/resource/acz11.pdf'})
    for pin,net in {'A':'ENC_A','C':'GND','B':'ENC_B','S1':'ENC_PUSH','S2':'GND'}.items():c.connect('SW3',pin,net)
    c.instance('Device:R_Small','R13','1k 1%',139.7,213.36)
    c.connect('R13','1','STATUS_LED_GP6',0,-5.08)
    c.connect('R13','2','STATUS_LED_A',0,5.08)
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    c.text('ENCODER',345.44,193.04)
    c.text('STATUS LED / GP6',121.92,195.58,1)
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    c.text('Capacitor positive terminals face BIAS_L / BIAS_R.\nBAT85S cathode is pin 1 (band). Clamps are not isolation.\nAll grounds common; route keyboard returns away from audio.\nRouted review draft; independent follow-up pending.',233.68,256.54,1)
    c.save()


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
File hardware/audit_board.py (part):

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
def usb(net):
    return any(s in net for s in (
        "USB_DP", "USB_DM", "_D+", "_D-", "Net-(U1-GPIO0)", "Net-(U1-GPIO1)"
    ))


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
